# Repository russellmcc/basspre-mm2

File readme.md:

# Basspre MM2

This is an open-source bass pre-amp meant for internal use in active basses with humbucker
inputs.  The circuit is a tribute to the classic 2-band pre-amp used in the
original MusicMan Stingray, with a few modifications.

Board layout and schematic files are in EAGLE format, while the simulations are
done in LT-SPICE.

The pre-amp has a buffered input to maintain very low thermal noise, it uses a rail-splitter IC
instead of a resistor divider to ensure clean tone with very low power, and
the voicing is modified to be less treble-heavy to ensure low EM interference.

[PDF Schematic](schem.pdf)

[OSH Park Link](https://oshpark.com/shared_projects/A13YAxJk)

Here's some simulations and tests of the voicing at various pot positions:

## Flat

### Simulation

## Bass Cut

### Simulation

## Bass Boost

### Simulation

### Test

## Treble Cut

### Simulation

## Treble Boost

### Simulation

### Test

## Both Boost

### Simulation

### Test

## Both Cut

### Simulation

### Test

Copyright 2014, Russell McClellan, all rights reserved.

<br /><span xmlns:dct="http://purl.org/dc/terms/" property="dct:title">Basspre MM-2</span> by <a xmlns:cc="http://creativecommons.org/ns#" href="russellmcc.com" property="cc:attributionName" rel="cc:attributionURL">Russell McClellan</a> is licensed under a <a rel="license" href="http://creativecommons.org/licenses/by-sa/4.0/">Creative Commons Attribution-ShareAlike 4.0 International License</a>.

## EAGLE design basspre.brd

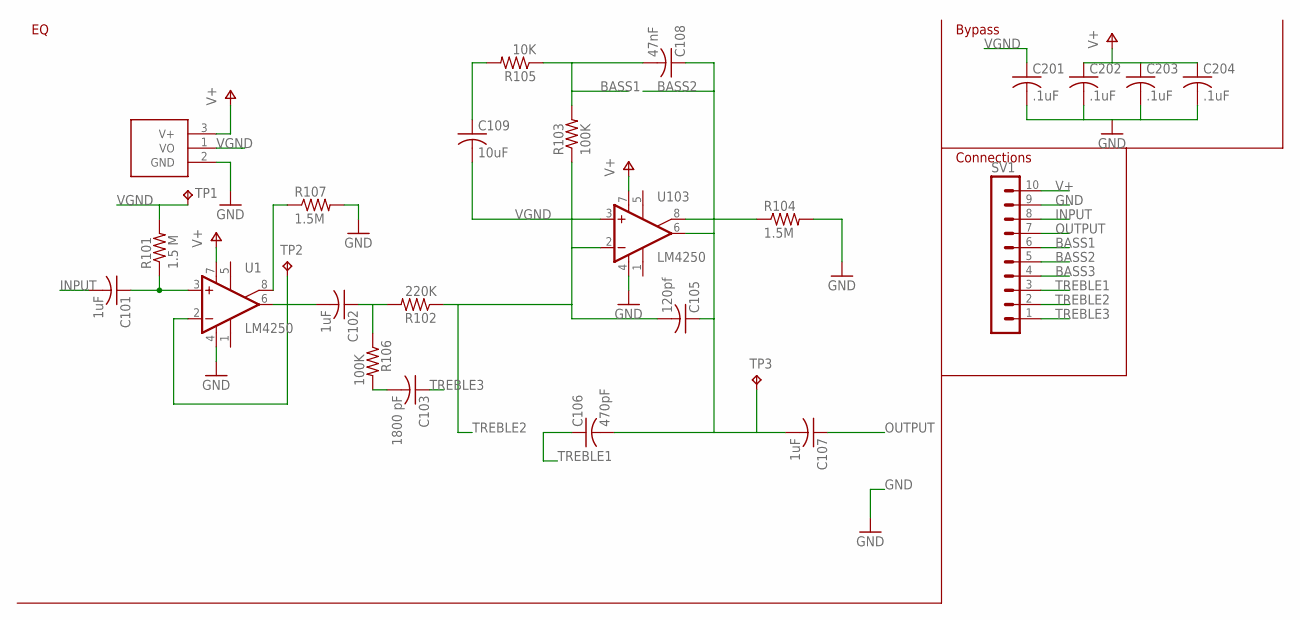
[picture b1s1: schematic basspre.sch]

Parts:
C101, C102, C107: 1uF; C0805
C103: 1800 pF; C0603
C105: 120pf; C0603
C106: 470pF; C0603
C108: 47nF; C0603
C109: 10uF; C0805
C201, C202, C203, C204: .1uF; C0603
R101: 1.5 M; R0603
R102: 220K; R0603
R103, R106: 100K; R0603
R104, R107: 1.5M; R0603
R105: 10K; R0603
SV1: MA10-1
TP1, TP2, TP3: TPPAD1-13; P1-13
U1, U103: LM4250; SOIC8
U101: TLE2426IDR; SOIC8

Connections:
BASS1: C108.2, R103.2, R105.1, SV1.6
BASS2: C105.1, C106.2, C107.2, C108.1, SV1.5, TP3.TP, U103.6 (OUT)
BASS3: SV1.4
C1: C101.1, R101.1, U1.3 (+IN)
GND: C201.2, C202.2, C203.2, C204.2, R104.2, R107.2, SV1.9, U1.4 (V-), U101.2 (GND), U103.4 (V-)
INPUT: C101.2, SV1.8
unnamed: C102.1, R102.2, R106.1
unnamed: R104.1, U103.8 (CURRENT)
unnamed: C102.2, TP2.TP, U1.2 (-IN), U1.6 (OUT)
unnamed: C109.1, R105.2
unnamed: C103.2, R106.2
OUTPUT: C107.1, SV1.7
R107: R107.1, U1.8 (CURRENT)
TREBLE1: C106.1, SV1.3
TREBLE2: C105.2, R102.1, R103.1, SV1.2, U103.2 (-IN)
TREBLE3: C103.1, SV1.1
V+: C202.1, C203.1, C204.1, SV1.10, U1.7 (V+), U101.3 (V+), U103.7 (V+)
VGND: C109.2, C201.1, R101.2, TP1.TP, U101.1 (VO), U103.3 (+IN)

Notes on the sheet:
Bypass
Connections

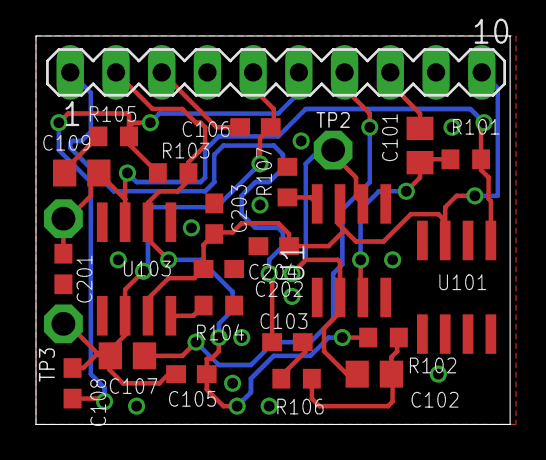
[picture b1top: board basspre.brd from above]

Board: 2 copper layers, 26.3 x 21.6 mm, 27 parts (1 on the bottom side), 17 nets.

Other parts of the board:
U$1: OSHW-LOGO-L

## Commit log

2014-06-18 initial
2014-06-23 minimal work
2014-07-05 initial layout
2014-07-05 added silkscreen started (rough) sim
2014-07-05 fix up values
2014-07-06 added simulations, changed some values around
2014-07-06 added pictures from simulations
2014-07-06 switched to 10 pin system so bass pot can be three terminal in future revisions without changing connection.
2014-07-06 switched to two lm4250s for micropower operation, added readme
2014-07-06 moved graphs to separate folder, added license
2014-07-06 notes on formats
2014-07-06 no dash
2014-07-06 changed bypass caps to 0805.
2014-07-06 added mouser order
2014-07-07 tent all the vias
2014-07-07 redid layout to be smaller
2014-07-07 added labeling silkscreens
2015-01-26 Added some test plots
2016-12-25 Add Schematic PDF
2016-12-25 no image pdf links
2016-12-25 Add osh park link

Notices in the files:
basspre.brd:
(c) 2014
CC-BY-SA
parts and their libraries:
SparkFun: Licensing: CC v3.0 Share-Alike You are welcome to use this library for commercial purposes.
